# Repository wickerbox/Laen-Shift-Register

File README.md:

# Laen's Shift Register Demo v2

This is a project to convert Laen's shift register demonstration design into KiCad. The demo board provides eight output LEDs driven by an HC595 shift register with input press-buttons for data, clock, and latch.  

Each press of the clock button queues up the status of the data button; press the latch button to show the outputs. Reset everything by pressing the master reset button followed by the latch button.

The boards can be chained together by the connectors at each end. 

I've <a href="https://oshpark.com/projects/dWEtqIvz">shared the boards at OSH Park</a>, where you can buy a set of three for $28.85.

|Ref|Qty|Description|MF_Name|MF_PN|Digikey PN|
|---|---|-----------|-------|-----|----------|
|C1|1|CAP CER 0.33UF 50V X7R RADIAL|TDK|FK24X7R1H334K|445-5263-ND|
|C2-C3|2|CAP CER 0.1UF 50V C0G RADIAL|TDK|FK26C0G1H104J|445-8532-ND|
|J1|1|HEADER MALE 6POS TH 1x06 0.1”|Harwin|M20-9992046|952-1902-ND|
|J2|1|CONN TERM SCREW GREEN 2.54MM 2POS TH|OnShoreTech|OSTVN02A150|ED10561-ND|
|J3|1|HEADER FEMALE 6POS TH 1x06 0.1”|Harwin|M20-7820642|952-1808-ND|
|LED0-7|8|LED RED DIFF 5MM ROUND T/H|Marktech Opto|MT4118-HR-A|1125-1188-ND|
|LED8-10|3|LED GRN DIFF 5MM ROUND T/H|Marktech Opto|MT2118-G-A|1125-1184-ND|
|R0-R7|8|RES 150 OHM 1/4W 5% CF MINI|Stackpole|CFM14JT150R|S150QCT-ND|
|R8-R12|5|RES 1K OHM 1/4W 5% CF MINI|Stackpole|CFM14JT1K00|S1KQCT-ND|
|SW1-4|4| SWITCH TACTILE SPST-NO 0.05A 24V |Omron|B3F-1000|SW400-ND|
|U1|1|IC REG LDO 5V 1A NCP7805 TO220AB|ON Semi|NCP7805TG|NCP7805TGOS-ND|
|U2|1|IC 8-BIT SHIFT REGISTER 16-DIP|TI|SN74HC595N|296-1600-5-ND|

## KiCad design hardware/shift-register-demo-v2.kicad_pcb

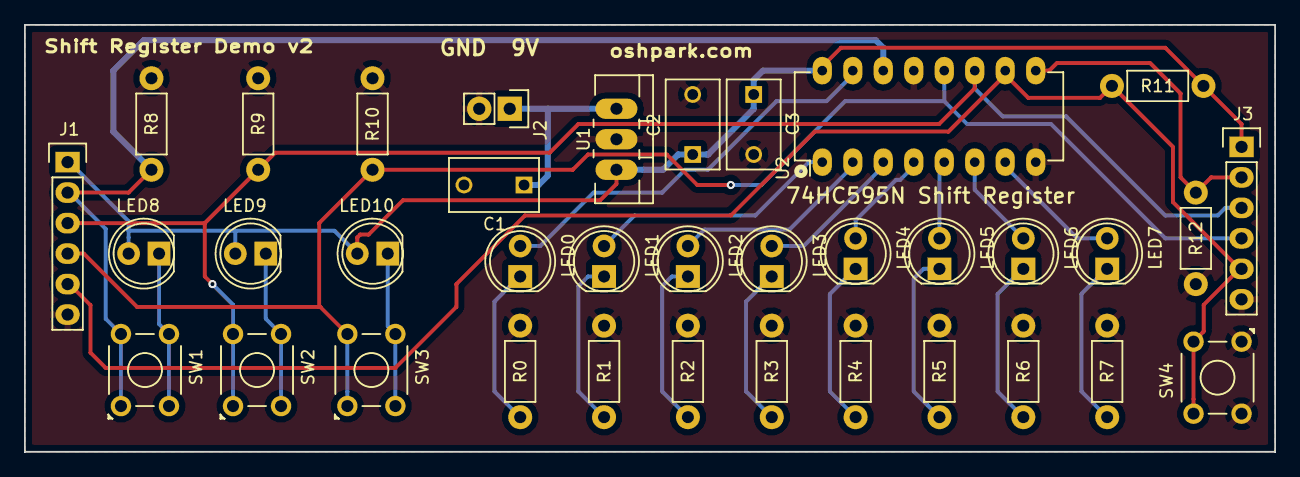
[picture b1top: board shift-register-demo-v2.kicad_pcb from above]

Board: 2 copper layers, 104.1 x 35.6 mm, 36 parts (0 on the bottom side), 27 nets.

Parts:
C1: 330nF; CAP-DISC-D7.5MM-P5MM
C2, C3: 100nF; CAP-DISC-D7.5MM-P5MM
J1: CONN_01x06; CONN-HEADER-STRAIGHT-P2.54MM-1x06
J2: VIN; CONN-ONSHORE-SCREW-GREEN-2PIN-TH
J3: CONN-1X06; CONN-HEADER-STRAIGHT-P2.54MM-1x06
LED0, LED1, LED2, LED3, LED4, LED5, LED6, LED7: RED; LED-D5MM-2PIN
LED8, LED9, LED10: GREEN; LED-D5MM-2PIN
R0, R1, R2, R3, R4, R5, R6, R7: 150; RES-CARBONFILM-7MM
R8, R9, R10, R11, R12: 1K; RES-CARBONFILM-7MM
SW1: DATA; SWITCH-OMRON-MOMENTARY-TH-B3F-10XX
SW2: CLOCK; SWITCH-OMRON-MOMENTARY-TH-B3F-10XX
SW3: LATCH; SWITCH-OMRON-MOMENTARY-TH-B3F-10XX
SW4: RESET; SWITCH-OMRON-MOMENTARY-TH-B3F-10XX
U1: NCP7805; TO-220-NEUTRAL123-VERT-LONGPADS
U2: 74HC595; DIP-16-W7.62MM-LONGPADS

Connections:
+5V: C2.1, C3.1, J1.1, J3.1, LED8.2, LED9.2, LED10.2, R11.1, U1.3, U2.16
+9V: C1.1, J2.1, U1.1
/CLOCK: J1.3, J3.3, R9.1, SW2.1, SW2.2, U2.11
/LATCH: J1.4, J3.4, R10.1, SW3.1, SW3.2, U2.12
/RESET: J1.5, J3.5, R11.2, SW4.3, SW4.4, U2.10
/SERIAL_DATA_IN: J1.2, R8.1, SW1.1, SW1.2, U2.14
/SERIAL_DATA_OUT: J3.2, R12.1, U2.9
GND: C1.2, C2.2, C3.2, J1.6, J2.2, J3.6, R0.2, R1.2, R2.2, R3.2, R4.2, R5.2, R6.2, R7.2, R8.2, R9.2, R10.2, R12.2, SW4.1, SW4.2, U1.2, U2.8, U2.13
unnamed: LED0.1, R0.1
unnamed: LED0.2, U2.15
unnamed: LED1.1, R1.1
unnamed: LED1.2, U2.1
unnamed: LED2.1, R2.1
unnamed: LED2.2, U2.2
unnamed: LED3.1, R3.1
unnamed: LED3.2, U2.3
unnamed: LED4.1, R4.1
unnamed: LED4.2, U2.4
unnamed: LED5.1, R5.1
unnamed: LED5.2, U2.5
unnamed: LED6.1, R6.1
unnamed: LED6.2, U2.6
unnamed: LED7.1, R7.1
unnamed: LED7.2, U2.7
unnamed: LED8.1, SW1.3, SW1.4
unnamed: LED9.1, SW2.3, SW2.4
unnamed: LED10.1, SW3.3, SW3.4

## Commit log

2016-09-09 Releasing v2 and the README description.
2016-09-09 Added to README.
